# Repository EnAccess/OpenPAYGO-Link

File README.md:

# OpenPAYGO Link

## What is OpenPAYGO Link?

OpenPAYGO Link (OPLink) is an open-source communication protocol for interfacing Solar Home Systems (SHS) with appliances and accessories. It allows you to easily make your SHS and appliances communicate with each other for features such as PAYGO locking of appliances, load-scheding, monitoring, etc. It includes both the hardware and software components needed to achieve communication from one SHS to multiple appliances over a single wire. 

## Key Features

* Very small footprint, can run on very restricted devices (e.g. STM8 with 1kB RAM and 8kB Flash)
* Half-duplex communication over a single wire with a multi-drop connection topology 
* Ensures reliable data transmission, even with different ground potentials between nodes 
* Supports variable-length payload 
* Supports standard request/reply and broadcast (to send requests to all appliances at once)
* The SHS (master) can automatically discover new appliances (slaves) and assign them a local address
* Slave nodes can instantly detect that they have been disconnected
* Slave nodes can directly send messages to the master (no need for polling from the master) 

It was designed to be used with Nexus Channel Core (based on the Open Connectivity Foundation communication standard) that provides standard resource model for common use cases. However, it is flexible enough that it can  be used with other application layers. 

**Limitations:**

There are a few limitations that are the result of compromises to keep the system as lightweight as possible. 

* The system is not intended to transmit large amount of data
* A node can only handle one request at a time
* The system can be slow if there are a lot of slaves on the bus
* The master needs to poll the appliances to detect that they have been disconnected

## Getting Started

This repository has resources to help you get started with adding OpenPAYGO Link to your SHS and/or appliance. There are a few options depending on your stage of development: 

**1. The STM8-based development board:** this small PCB includes the hardware required for OpenPAYGO Link (MCU + transceiver) as well as a buck converter to supply power from the power line, a switch controlled by the MCU, a push-button and an LED to facilitate testing. It is provided with an example firmware to get you started quickly (see ["Examples"](Examples/)). You can just drop the dev board into a prototype to have it control the switch in an appliance. 

**2. The STM8-based addon board:** this small PCB includes the bare minimum required for OpenPAYGO Link. You can add this addon board to an existing PCB as a way to quickly add OpenPAYGO Link to your system while not making any changes to the main MCU of your system. The addon board communicates with your main MCU through a simple GPIO to make it as easy as possible to use as all of the OpenPAYGO Link system is handled by the addon board. It is also provided with an example firmware (see ["Examples"](Examples/)). 

**3. Adapt the library for your main MCU:** This is the most cost efficient method as it does not require a secondary MCU just for OpenPAYGO Link. However, it requires more engineering as you need to develop some hardware abstractions to allow the OpenPAYGO Link library to use your device (see ["OPL"](OPL/)). This also requires your MCU to be compatible with 9-bit multiprocessor UART, which is very common but some MCU might not be supported. We keep a list of some MCUs known to be compatible with OpenPAYGO Link [here](Documentation/compatible_mcus.md). 

*OpenPAYGO Link STM8 Development Board* 

## What's next? 

As the core of the features are implemented, we will focus our future efforts in adding more examples to help make it easier to adopt OpenPAYGO Link even for more complex use cases. In particular, we will focus on adding an example development board and addon board based on STM32 that will showcase more advanced use cases with more Nexus Channel Core endpoints and provide a basis to start more complex projects. 

We are welcoming external contribution to the projects, and we would be very happy to accept pull requests for implementation on any other MCU targets to make it easier for people to add OpenPAYGO Link to their main MCU as quickly as possible. 

You can track all of the new features and changes to the project in the [Changelog](CHANGELOG.md).

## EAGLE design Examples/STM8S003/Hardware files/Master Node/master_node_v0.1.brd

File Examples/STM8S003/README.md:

# OpenPAYGO Link STM8S examples
This directory contains a set of basic usage examples of the OpenPAYGO Link package on a STM8SX03 microcontroller. The examples use a minimal custom Hardware Abstraction Layer and require no external libraries. 

Due to the very limited resources of this MCU, these examples are meant to showcase the core features of OpenPAYGO Link used with Nexus Channel Core and provide a basis for people wanting to implement simple use cases into their devices at a low cost. 

## Target
The STM8SX03 is an inexpensive microcontroller with 8kB of flash and 1kB or RAM and a maximum clock speed of 16MHz (in all the examples the clock is set to the default speed of 2MHz). Either the STM8S003F3P6 or the STM8S103F3P6 can be used, the only difference between them being that the first one supports less flash write cycles. There are development boards that include these microcontrollers like the STM8S003 Discovery board from ST or the [STM8S003/103](https://tenbaht.github.io/sduino/hardware/stm8blue/) "blue pill" boards.

## Schematic
Although the provided schematic is for the STMSX03 targets, the connections between the LIN transceiver and any other microcontroller should be equivalent.

## Build/Flash
The projects are built using Make and [Small Device C Compiler](http://sdcc.sourceforge.net/) (SDCC). This compiler supports different targets including a couple of STM8S variants, which need to be defined in the MCU field of the *Makefile.include* file. Either "stm8s003f3" or "stm8s103f3" will work.

It is necessary to clean with before compiling the project for a new/different node (master or slave), otherwise the build will fail. After compiling *main.hex* will be created in the same directory as *main.c*. This file can be used to flash the target.

There are different programming CLI tools available: [ST Visual Programmer](https://www.st.com/en/development-tools/stvp-stm8.html) (STVP) for Windows (which also comes with a GUI) and [stm8flash](https://github.com/vdudouyt/stm8flash) for Linux/MacOS.

## TODO
* Update Makefile.include to add support for Linux/MacOS commands and tools.

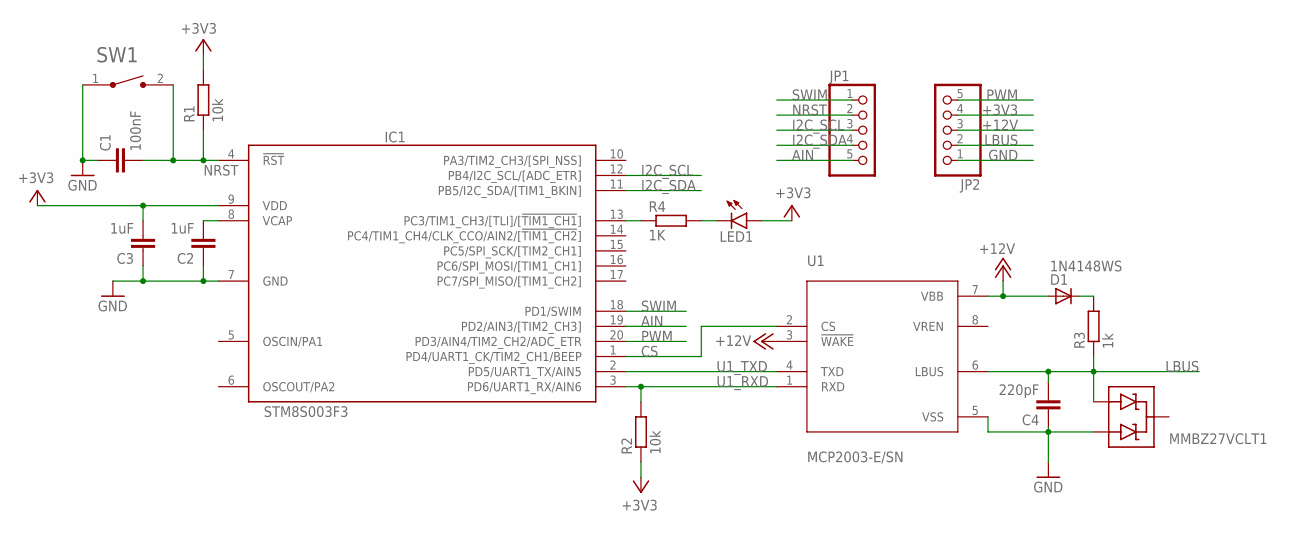
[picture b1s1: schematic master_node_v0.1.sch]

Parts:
C1: 100nF; C0603
C2, C3: 1uF; C0603
C4: 220pF; C0603
D1: 1N4148WS; SOD323
D2: MMBZ27VCLT1; SOT23-3
IC1: STM8S003F3; TSSOP20
JP1, JP2: PINHD-1X5; 1X05
LED1: LEDCHIP-LED0603; CHIP-LED0603
R1, R2: 10k; R0603
R3: 1k; R0603
R4: 1K; R0603
SW1: FSMSM; TE_FSMSM
U1: MCP2003-E/SN; SOIC127P600X175-8N

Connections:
+3V3: C3.2, IC1.9 (VDD), JP2.4, LED1.A, R1.2, R2.1
+12V: D1.A, JP2.3, U1.3 (!WAKE), U1.7 (VBB)
AIN: IC1.19 (PD2/AIN3/[TIM2_CH3]), JP1.5
CS: IC1.1 (PD4/UART1_CK/TIM2_CH1/BEEP), U1.2 (CS)
GND: C1.1, C2.1, C3.1, C4.1, D2.1 (A1), IC1.7 (GND), JP2.1, SW1.1, U1.5 (VSS)
I2C_SCL: IC1.12 (PB4/I2C_SCL/[ADC_ETR]), JP1.3
I2C_SDA: IC1.11 (PB5/I2C_SDA/[TIM1_BKIN]), JP1.4
LBUS: C4.2, D2.2 (A2), JP2.2, R3.1, U1.6 (LBUS)
unnamed: D1.C, R3.2
unnamed: C2.2, IC1.8 (VCAP)
unnamed: LED1.C, R4.2
unnamed: IC1.13 (PC3/TIM1_CH3/[TLI]/[!TIM1_CH1!]), R4.1
NRST: C1.2, IC1.4 (!RST), JP1.2, R1.1, SW1.2
PWM: IC1.20 (PD3/AIN4/TIM2_CH2/ADC_ETR), JP2.5
SWIM: IC1.18 (PD1/SWIM), JP1.1
U1_RXD: IC1.3 (PD6/UART1_RX/AIN6), R2.2, U1.1 (RXD)
U1_TXD: IC1.2 (PD5/UART1_TX/AIN5), U1.4 (TXD)

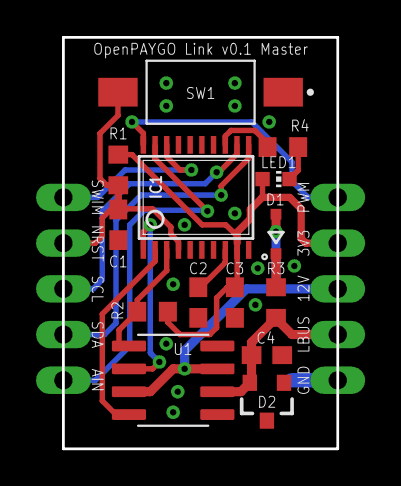
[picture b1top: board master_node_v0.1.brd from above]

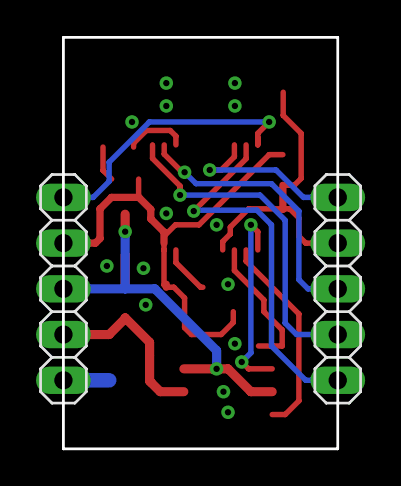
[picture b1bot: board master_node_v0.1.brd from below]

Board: 2 copper layers, 15.2 x 22.9 mm, 16 parts (2 on the bottom side), 17 nets.

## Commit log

2020-11-23 Beta version 0.1
2020-11-23 Update README.md
    Fix issue with schematic link in README
2020-11-23 Update README.md
    Fix issue with schematic view in readme
2020-11-24 Update README.md
    Clarified points in the README
2020-12-11 Release v0.1
2020-12-14 Improved documentation
2020-12-14 Update oplink_adapters.txt
    Instructions on the use of the oplink_adapter header.
2020-12-14 Added better render
2021-02-03 Update LICENSE
2024-09-19 Add `CODE_OF_CONDUCT.md`
2024-09-23 Add `.github/SECURITY.md`
2024-09-23 Add `.github/PULL_REQUEST_TEMPLATE.md`
2024-09-23 Add `.github/ISSUE_TEMPLATE/config.yml`
2024-09-23 Add `.github/ISSUE_TEMPLATE/feature_request.yml`
2024-09-23 Add `.github/ISSUE_TEMPLATE/bug_report.yml`
2024-09-23 Add `CONTRIBUTING.md`
2025-04-28 Add `DISCORD_ETIQUETTE.md`
